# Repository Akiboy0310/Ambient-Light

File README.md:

# Ambient-Light
In this project the colores of a light(neopixel) must change acording to the colors of the image that a monitor shows. To now wich color are in the Image shown by the monitor, four RGB-sensors(TCS3472) were used. To control the light and the RGB-sensors the esp32 was used.

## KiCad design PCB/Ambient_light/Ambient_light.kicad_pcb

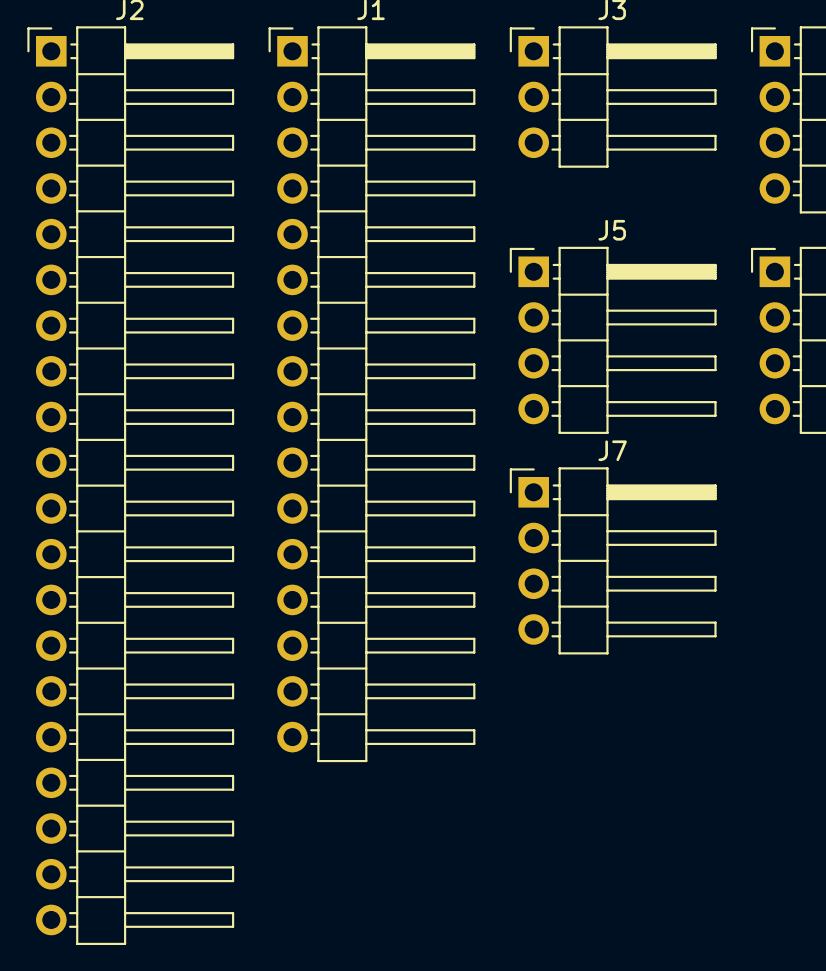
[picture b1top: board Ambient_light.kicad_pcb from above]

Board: 2 copper layers, 7 parts (0 on the bottom side), 5 nets, no tracks yet.

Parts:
J1: Conn_01x16_Female; Pin_Header_Angled_1x16_Pitch2.54mm
J2: Conn_01x20_Female; Pin_Header_Angled_1x20_Pitch2.54mm
J3: Conn_01x03_Female; Pin_Header_Angled_1x03_Pitch2.54mm
J4, J5, J6, J7: Conn_01x04_Female; Pin_Header_Angled_1x04_Pitch2.54mm

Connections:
unnamed: J1.5, J3.2
unnamed: J1.15, J3.3
unnamed: J2.4, J4.4, J5.4, J6.4, J7.4
unnamed: J2.18, J5.3, J7.3
unnamed: J3.1, J4.3, J6.3

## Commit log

2020-11-06 Update README.md
    project description added
2020-11-21 Neopixel programm crated but not finished
2020-11-25 working neopixel Code
2020-11-25 no changes
2020-11-25 Delete neopixel.zip
    deleted neopixel.zip
2020-11-25 added comments and did some changes
2020-12-05 WebGUI created with demo code as basis not finished
2020-12-10 Changes WEBGUI
2020-12-10 turning Neopixel with toggle switch on and of
2020-12-11 Neopixel can be turned on/of and the bridness can be set via the Web-GUI
2020-12-11 Color of Neopixels can be set via colorpicker
2020-12-13 little changes
2020-12-21 RGB Sensor read c r g b Values
2020-12-23 RGB sensor works
2020-12-28 addet rgb sensor to WebGUI Code
2020-12-31 Getting values from all 4 RGB-sensors
2021-01-01 color sensing with all 4 rgb sensor can be turned on and of with WebGUI
2021-01-01 all 4 areas of the led strip can be turned on and off seperatly
2021-01-03 3D Casing for the rgb sensors
2021-01-06 Save function added to webgui
2021-01-11 color sensing works fine
